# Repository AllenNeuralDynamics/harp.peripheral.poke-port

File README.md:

# harp.peripheral.delphi-poke

companion circuit board for Mouse "Poke" Port.

<p align="center">
  
&nbsp; &nbsp; &nbsp; &nbsp;
  
</p>

> [!NOTE]
> This repository is for the electronics hardware only. For the physical Poke Port, see the [CAD Model](https://cad.onshape.com/documents/066d94ed47eba590ef197816/w/7206c419a0e3b3641e025c3e/e/6c7b2bb3fef528a1d7258398) (Onshape).

## Assembly

## Installation

For installing the Poke Port into a mouse home cage, we recommend drilling out a 25mm hole with a hole saw ([example](https://www.mcmaster.com/products/hole-saws/diameter~25-mm/)), and installing M3 heat-set inserts into the home cage for threaded mounting.

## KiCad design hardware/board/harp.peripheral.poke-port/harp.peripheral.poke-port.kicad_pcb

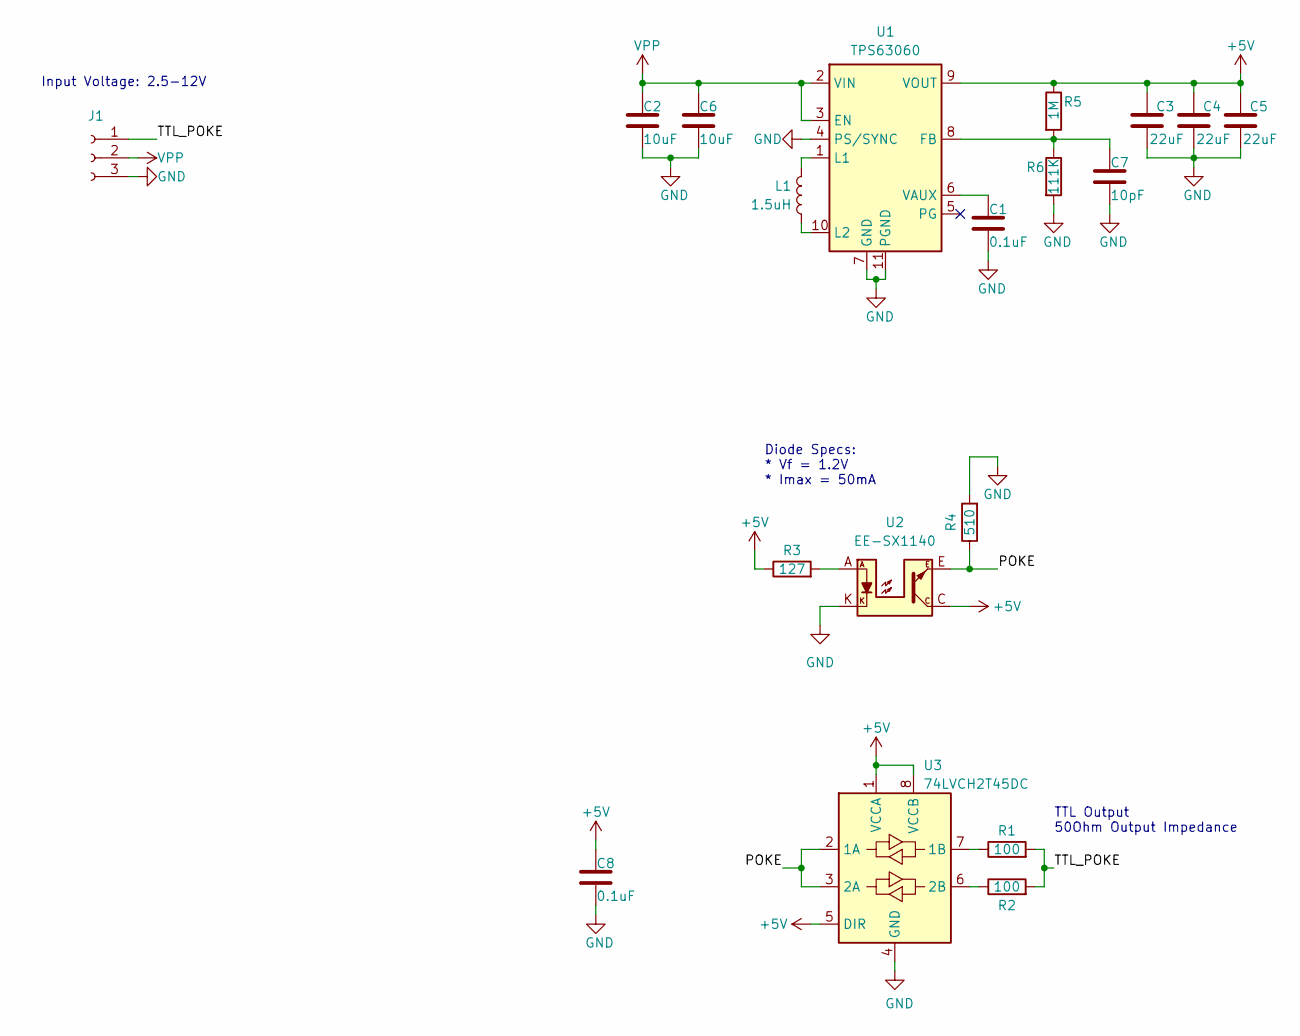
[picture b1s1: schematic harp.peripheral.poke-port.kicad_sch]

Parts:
C1, C8: 0.1uF; C_0603_1608Metric
C2, C6: 10uF; C_0805_2012Metric
C3, C4, C5: 22uF; C_0805_2012Metric; Rated Voltage 10V
C7: 10pF; C_0402_1005Metric
J1: Conn_01x03_Socket; 3M_Mini-Clamp-Socket-37203-62B3-003PL-1x3_Vertical
L1: 1.5uH; L_Murata_1226AS-H-1R5N=P2
R1, R2: 100; R_0603_1608Metric; Tolerance 1%
R3: 127; R_0603_1608Metric
R4: 510; R_0603_1608Metric; Tolerance 1%
R5: 1M; R_0402_1005Metric
R6: 111K; R_0402_1005Metric
U1: TPS63060; Texas_S-PWSON-N10_ThermalVias
U2: EE-SX1140
U3: 74LVCH2T45DC; VSSOP-8_2.3x2mm_P0.5mm

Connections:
+5V: C3.2, C4.2, C5.2, C8.1, R3.1, R5.1, U1.9 (VOUT), U2.C, U3.1 (VCCA), U3.5 (DIR), U3.8 (VCCB)
/POKE: R4.1, U2.E, U3.2 (1A), U3.3 (2A)
/TTL_POKE: J1.1, R1.2, R2.2
GND: C1.2, C2.2, C3.1, C4.1, C5.1, C6.2, C7.2, C8.2, J1.3, R4.2, R6.2, U1.4 (PS/SYNC), U1.7 (GND), U1.11 (PGND), U2.K, U3.4 (GND)
unnamed: R3.2, U2.A
unnamed: C7.1, R5.2, R6.1, U1.8 (FB)
unnamed: L1.1, U1.1 (L1)
unnamed: L1.2, U1.10 (L2)
unnamed: C1.1, U1.6 (VAUX)
unnamed: R1.1, U3.7 (1B)
unnamed: R2.1, U3.6 (2B)
VPP: C2.1, C6.1, J1.2, U1.2 (VIN), U1.3 (EN)

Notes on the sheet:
TTL Output 50Ohm Output Impedance
Input Voltage: 2.5-12V
Diode Specs: * Vf = 1.2V * Imax = 50mA

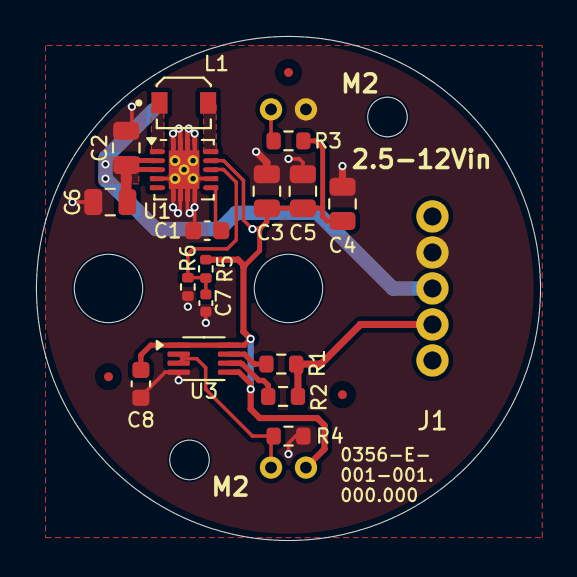
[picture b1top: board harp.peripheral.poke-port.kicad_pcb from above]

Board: 2 copper layers, 28.0 x 28.0 mm, 19 parts (1 on the bottom side), 12 nets.

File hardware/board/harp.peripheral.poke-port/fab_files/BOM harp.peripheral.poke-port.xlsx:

Designator | Digikey PN | Man. # | Manufacturer | Description | Footprint | QTY | Designation
C7 | 1276-1139-1-ND | CL05C100JB5NNNC | Samsung Electro-Mechanics | CAP CER 10PF 50V C0G/NP0 0402 | C_0402_1005Metric | 1 | 10pF
C4,C5,C3 | 1276-CL21A226MAYNNNECT-ND | CL21A226MAYNNNE | Samsung Electro-Mechanics | CAP CER 22UF 25V X5R 0805 | C_0805_2012Metric | 3 | 22uF
U1 | 296-30204-1-ND | TPS63060DSCR | TI | IC REG BUCK BOOST ADJ 2A 10WSON | Texas_S-PWSON-N10_ThermalVias | 1 | TPS63060
R1,R2 | 2019-RK73H1JTTD1000FCT-ND | RK73H1JTTD1000F | KOA Speer Electronics, Inc | RES 100 OHM 1% 1/8W 0603 | R_0603_1608Metric | 2 | 100
R4 | 2019-SG73P1JTTD5100FCT-ND | SG73P1JTTD5100F | KOA Speer Electronics, Inc. | RES 510 OHM 1% 1/3W 0603 | R_0603_1608Metric | 1 | 510
R3 | 541-127HCT-ND | CRCW0603127RFKEA | Vishay Dale | RES SMD 127 OHM 1% 1/8W 0603 | R_0603_1608Metric | 1 | 127
R6 | 2019-RN73H1ETTP1113F25CT-ND | RN73H1ETTP1113F25 | KOA Speer Electronics, Inc. | RES 111K OHM 1% 1/16W 0402 | R_0402_1005Metric | 1 | 111K
C8,C1 | 478-KGM15BR71H104JTCT-ND | KGM15BR71H104JT | Kyocera | CAP CER 0.1UF 50V X7R 0603 | C_0603_1608Metric | 2 | 0.1uF
C6,C2 | 1276-6454-1-ND | CL21A106KAYNNNG | Samsung Electro-Mechanics | CAP CER 10UF 25V X5R 0805 | C_0805_2012Metric | 2 | 10uF
L1 | 490-14150-1-ND | 1226AS-H-1R5N=P2 | Murata | FIXED IND 1.5UH 2.9A 37 MOHM SMD | L_Murata_1226AS-H-1R5N=P2 | 1 | 1.5uH
R5 | 541-MCS0402MD1004BE000CT-ND | MCS0402MD1004BE000 | Vishay Dale | RES 1M OHM 0.1% 1/16W 0402 | R_0402_1005Metric | 1 | 1M
U3 | 1727-4596-1-ND | 74LVCH2T45DC | TI | IC XLTR VL BIDIR 8-VSSOP | VSSOP-8_2.3x2mm_P0.5mm | 1 | 74LVCH2T45DC
J1 | 3M5701-ND | 37203-62B3-003PL | 3M | CONN RCPT 3POS 0.079 GOLD PCB | 3M_Mini-Clamp-Socket-37203-62B3-003PL-1x3_Vertical | 1 | Conn_01x03_Socket
U2 | OR1034-ND | EE-SX1140 | Omron | SENSOR OPT SLOT PHOTOTRAN PCB MT | EE-SX1140 | 1 | EE-SX1140

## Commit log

2025-02-03 fix merge conflicts
2025-02-03 add 3d models
2025-02-03 update silkscreen
2025-03-06 add schematic errata note
2025-03-06 upload readme pics
2025-03-06 update photointerruptor silkscreen
2025-03-06 update photointerrupter resistor
2025-03-06 add license
2026-03-04 Vacuum port option
2026-03-06 Fab files for vacuum port
2026-04-15 update footprint model reference
2026-04-28 Fixed R4 -> 510ohm
